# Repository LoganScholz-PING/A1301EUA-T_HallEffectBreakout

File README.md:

# A1301EUA-T_HallEffectBreakout
Breakout board for A1301EUA-T SIP-3 hall effect sensor

datasheet link: https://media.digikey.com/pdf/Data%20Sheets/Allegro%20PDFs/A1301,02.pdf

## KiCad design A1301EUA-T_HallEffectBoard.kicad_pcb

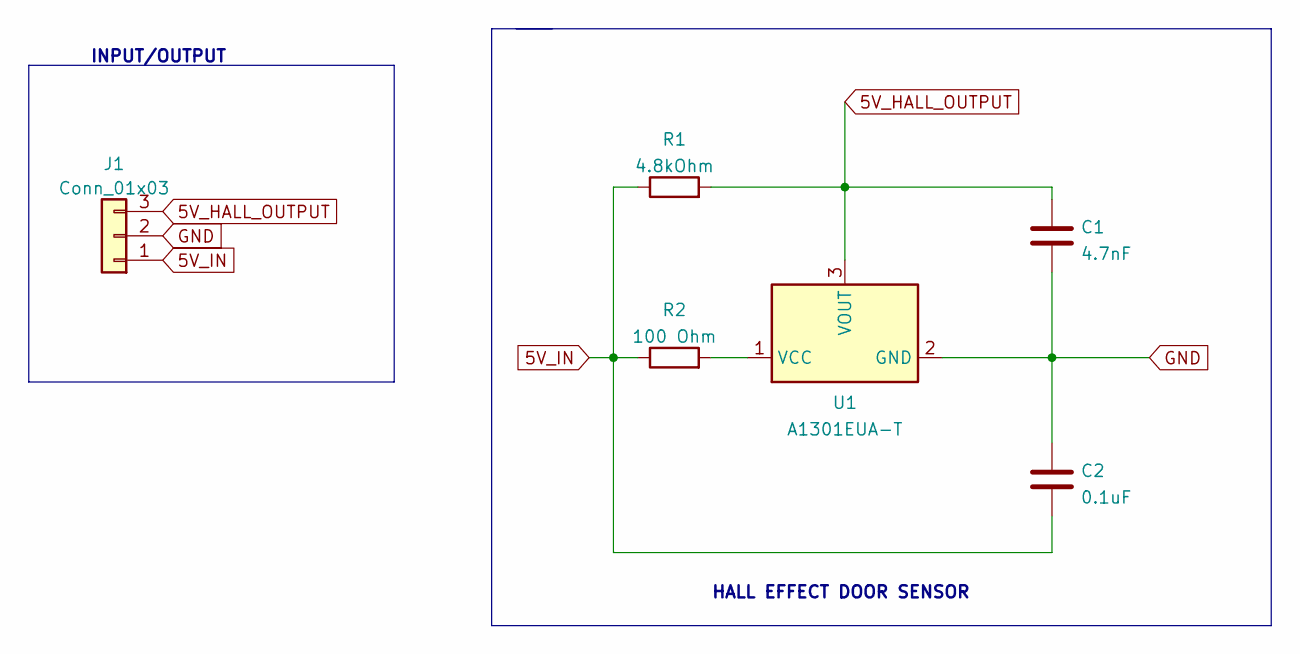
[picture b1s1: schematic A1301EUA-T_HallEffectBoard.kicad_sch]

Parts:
C1: 4.7nF; C_Disc_D6.0mm_W2.5mm_P5.00mm
C2: 0.1uF; C_Disc_D6.0mm_W2.5mm_P5.00mm
J1: Conn_01x03; PinHeader_1x03_P2.54mm_Vertical
R1: 4.8kOhm; R_Axial_DIN0207_L6.3mm_D2.5mm_P15.24mm_Horizontal
R2: 100 Ohm; R_Axial_DIN0207_L6.3mm_D2.5mm_P15.24mm_Horizontal
U1: A1301EUA-T; SIP3_11.6x8.5mm

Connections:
5V_HALL_OUTPUT: C1.1, J1.3, R1.2, U1.3 (VOUT)
5V_IN: C2.1, J1.1, R1.1, R2.1
GND: C1.2, C2.2, J1.2, U1.2 (GND)
unnamed: R2.2, U1.1 (VCC)

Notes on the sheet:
INPUT/OUTPUT
HALL EFFECT DOOR SENSOR

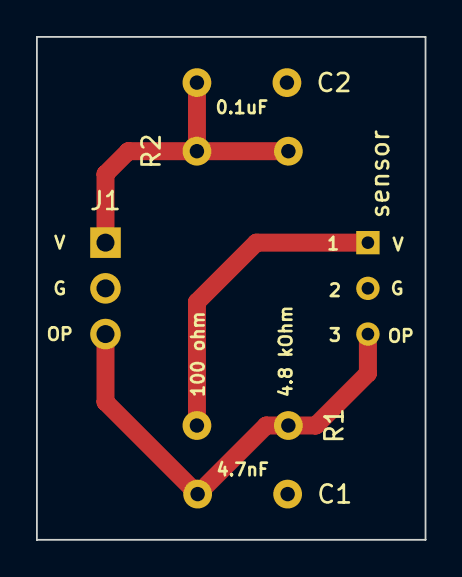
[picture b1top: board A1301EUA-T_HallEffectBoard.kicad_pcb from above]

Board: 2 copper layers, 21.6 x 27.9 mm, 6 parts (0 on the bottom side), 4 nets.

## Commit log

2022-06-22 added datasheet link
2022-06-22 initial commit - finished?
2022-06-23 submitted to JLCPCB
